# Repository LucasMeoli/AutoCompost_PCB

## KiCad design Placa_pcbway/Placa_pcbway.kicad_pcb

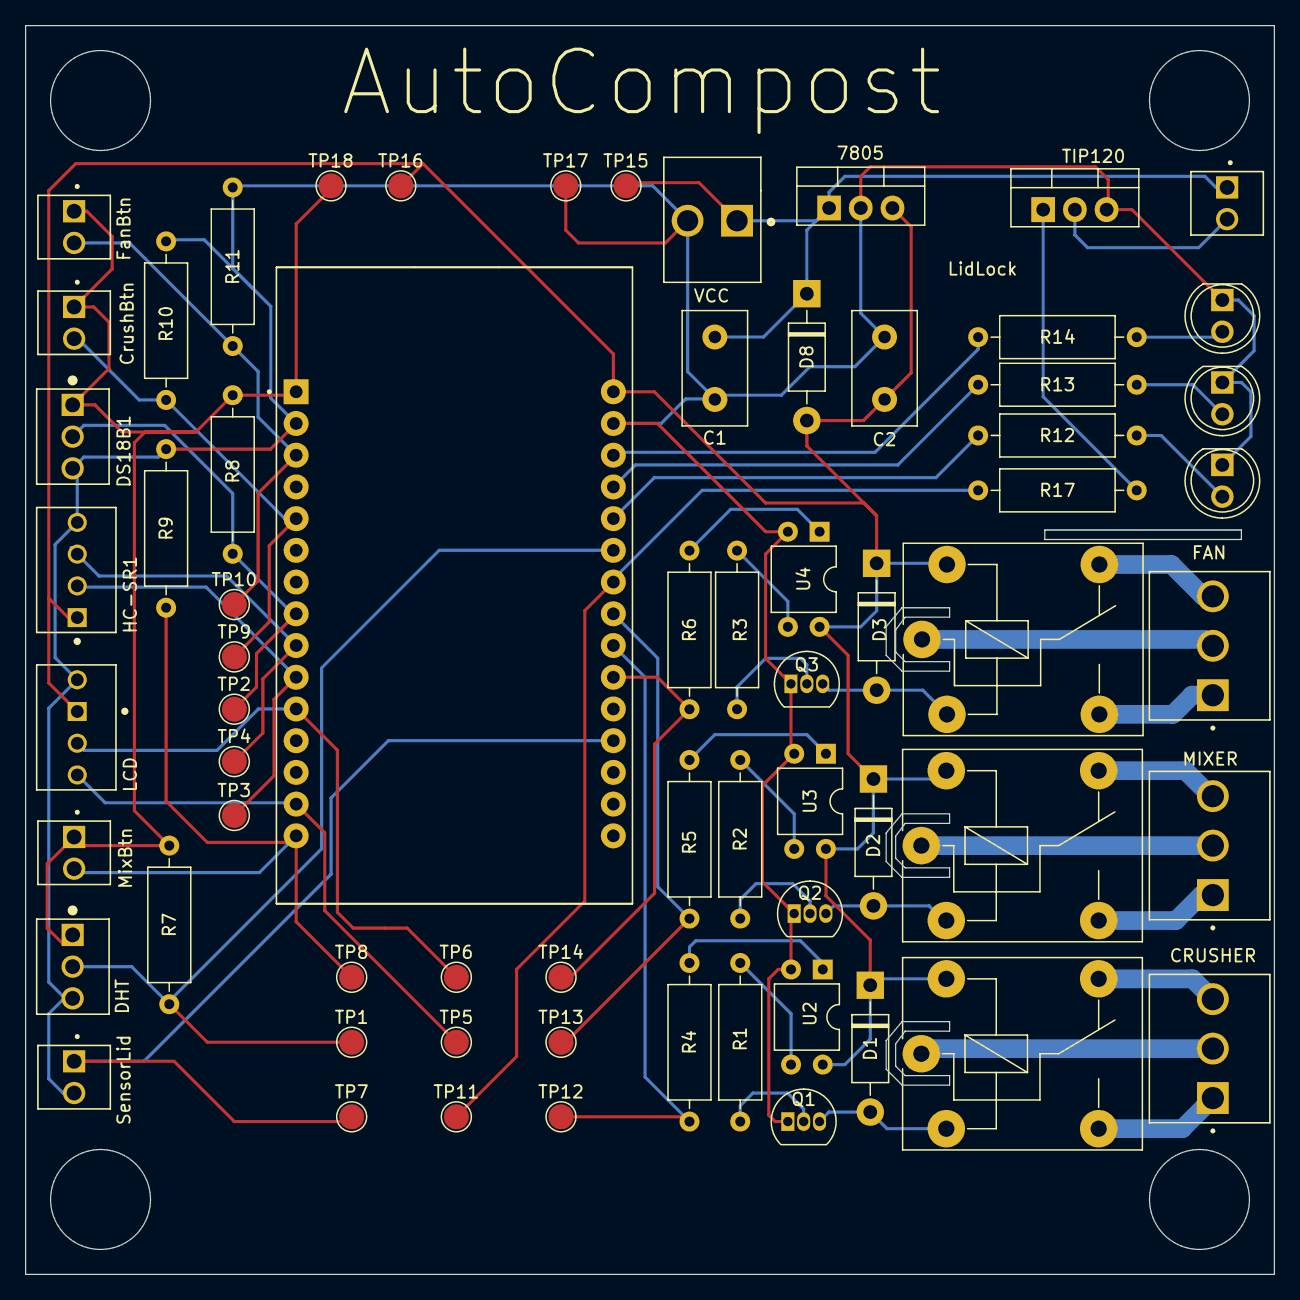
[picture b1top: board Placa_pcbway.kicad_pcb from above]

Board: 2 copper layers, 100.0 x 100.0 mm, 67 parts (0 on the bottom side), 47 nets.

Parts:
C1: 33nF; C_Disc_D9.0mm_W5.0mm_P5.00mm
C2: 100nF; C_Disc_D9.0mm_W5.0mm_P5.00mm
CrusherButton1: Molex 0.100; Molex_100_2pines
D1, D2, D3, D8: 1N4007; D_DO-41_SOD81_P10.16mm_Horizontal
D4, D5, D6: LED; LED_D5.0mm
DHT1: Molex 0.100; Molex_100_3pines
DS18B1: Molex 0.100; Molex_100_3pines
FanButton1: Molex 0.100; Molex_100_2pines
HC-SR1: Molex 0.100; Molex_100_4pines
J1, J2, J3: Molex 0.156; Molex_156_3pines
K1, K2, K3: FINDER-36.11; Relay_SPDT_Finder_36.11
LCD1: Molex 0.100; Molex_100_4pines
Lock1, Lock2: Molex 0.100; Molex_100_2pines
MixerButton1: Molex 0.100; Molex_100_2pines
Q1, Q2, Q3: 2N3904; TO-92_Inline
QLock1: TIP120; TO-220-3_Vertical
R1, R2, R3, R12, R13, R14: 220; R_Axial_DIN0309_L9.0mm_D3.2mm_P12.70mm_Horizontal
R4, R5, R6: 100; R_Axial_DIN0309_L9.0mm_D3.2mm_P12.70mm_Horizontal
R7, R8: 4k7; R_Axial_DIN0309_L9.0mm_D3.2mm_P12.70mm_Horizontal
R9, R10, R11: 10k; R_Axial_DIN0309_L9.0mm_D3.2mm_P12.70mm_Horizontal
R17: 2k2; R_Axial_DIN0309_L9.0mm_D3.2mm_P12.70mm_Horizontal
TP1, TP2, TP3, TP4, TP5, TP6, TP7, TP8, TP9, TP10, TP11, TP12, TP13, TP14, TP15, TP16, TP17, TP18: TestPoint; TestPoint_Pad_D2.0mm
U1: LM7805_TO220; TO-220-3_Vertical
U2, U3, U4: PC817; DIP-4_W7.62mm
U5: ESP32-DEVKIT-V1; MODULE_ESP32_DEVKIT_V1
Vext1: Molex 0.156; Molex_156_2pines

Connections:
5V: C2.1, D1.1 (K), D2.1 (K), D3.1 (K), D8.2 (A), HC-SR1.4, K1.A2, K2.A2, K3.A2, LCD1.2, TP16.1, U1.3 (VO), U2.4, U3.4, U4.4, U5.30 (VIN)
/3V3: CrusherButton1.1, DHT1.1, DS18B1.1, FanButton1.1, MixerButton1.1, R7.1, R8.1, TP18.1, U5.1 (3V3)
/Crusher: R4.1, TP12.1, U5.22 (D33)
/CrusherBtn: CrusherButton1.2, R10.2, TP9.1, U5.5 (D4)
/DHT: DHT1.2, R7.2, TP1.1, U5.25 (D27)
/DS18B20: DS18B1.2, R8.2, TP2.1, U5.8 (D5)
/Echo_HC-SR04: HC-SR1.2, TP4.1, U5.9 (D18)
/Fan: R6.1, TP14.1, U5.21 (D32)
/FanBtn: FanButton1.2, R11.2, TP10.1, U5.3 (D15)
/LCD_SCL: LCD1.4, TP5.1, U5.14 (D22)
/LCD_SDA: LCD1.3, TP6.1, U5.11 (D21)
/Led1: R12.2, U5.26 (D14)
/Led2: R13.2, U5.27 (D12)
/Led3: R14.2, U5.28 (D13)
/Lid: Lock1.1, TP7.1, U5.19 (D34)
/Lock: R17.2, TP11.1, U5.24 (D26)
/Mixer: R5.1, TP13.1, U5.23 (D25)
/MixerBtn: MixerButton1.2, R9.2, TP8.1, U5.15 (D23)
/Trig_HC-SR04: HC-SR1.3, TP3.1, U5.10 (D19)
/VCC: C1.1, D8.1 (K), Lock2.1, TP15.1, U1.1 (VI), Vext1.1
GND: C1.2, C2.2, D4.1 (K), D5.1 (K), D6.1 (K), DHT1.3, DS18B1.3, HC-SR1.1, LCD1.1, Lock1.2, Q1.1 (E), Q2.1 (E), Q3.1 (E), QLock1.3 (E), R9.1, R10.1, R11.1, TP17.1, U1.2 (GND), U2.2, U3.2, U4.2, U5.2 (GND), U5.29 (GND), Vext1.2
unnamed: D1.2 (A), K1.A1, Q1.3 (C)
unnamed: D2.2 (A), K2.A1, Q2.3 (C)
unnamed: D3.2 (A), K3.A1, Q3.3 (C)
unnamed: D4.2 (A), R12.1
unnamed: D5.2 (A), R13.1
unnamed: D6.2 (A), R14.1
unnamed: J1.1, K1.14
unnamed: J1.2, K1.11
unnamed: J1.3, K1.12
unnamed: J2.1, K2.14
unnamed: J2.2, K2.11
unnamed: J2.3, K2.12
unnamed: J3.1, K3.14
unnamed: J3.2, K3.11
unnamed: J3.3, K3.12
unnamed: Q1.2 (B), R1.2
unnamed: Q2.2 (B), R2.2
unnamed: Q3.2 (B), R3.2
unnamed: QLock1.1 (B), R17.1
unnamed: Lock2.2, QLock1.2 (C)
unnamed: R1.1, U2.3
unnamed: R2.1, U3.3
unnamed: R3.1, U4.3
unnamed: R4.2, U2.1
unnamed: R5.2, U3.1
unnamed: R6.2, U4.1

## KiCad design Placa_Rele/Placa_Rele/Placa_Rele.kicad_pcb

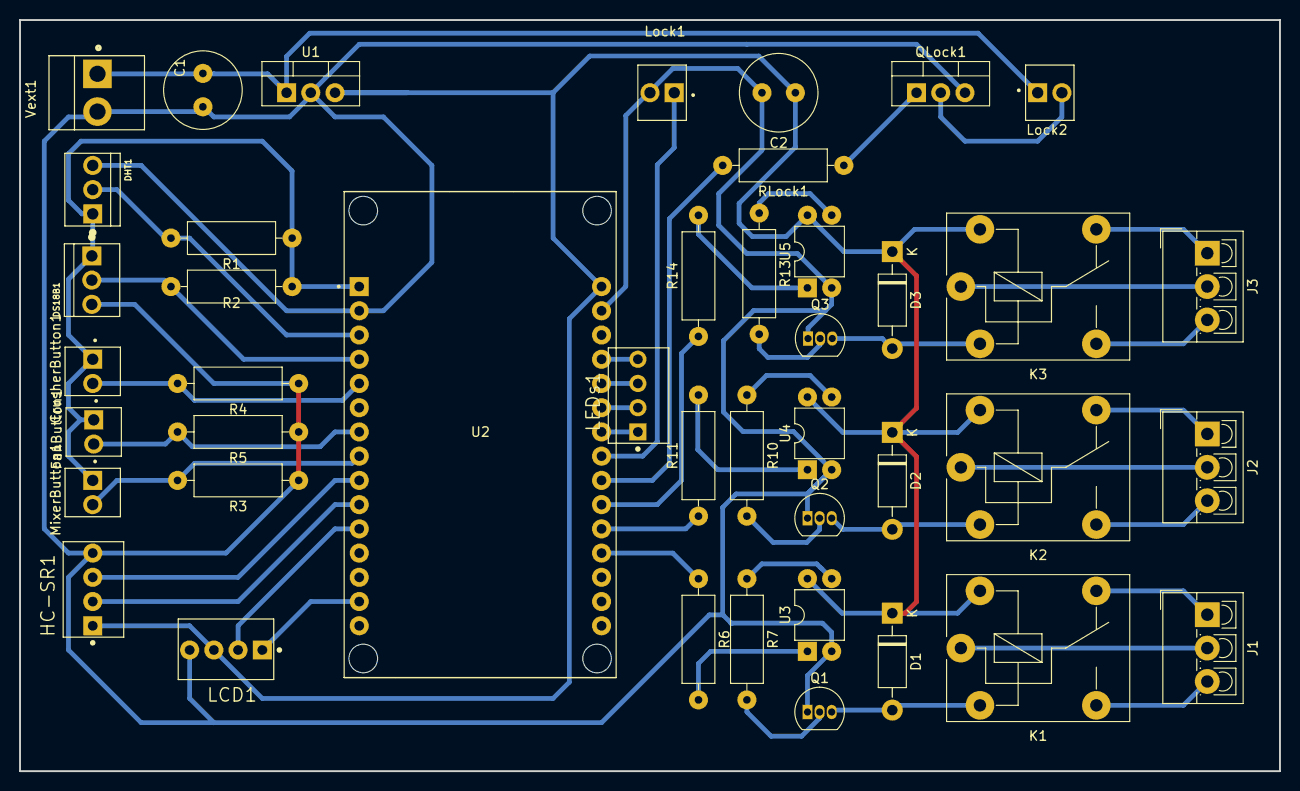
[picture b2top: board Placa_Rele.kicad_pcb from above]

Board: 2 copper layers, 132.1 x 78.7 mm, 43 parts (0 on the bottom side), 45 nets.

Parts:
C1: 33nF; C_Radial_D8.0mm_H7.0mm_P3.50mm
C2: 100nF; C_Radial_D8.0mm_H7.0mm_P3.50mm
CrusherButton1: Molex 0.100; Molex_100_2pines
D1, D2, D3: 1N4007; D_DO-41_SOD81_P10.16mm_Horizontal
DHT1: Molex 0.100; Molex_100_3pines
DS18B1: Molex 0.100; Molex_100_3pines
FanButton1: Molex 0.100; Molex_100_2pines
HC-SR1: Molex 0.100; Molex_100_4pines
J1: Screw_Terminal_Crusher1; TerminalBlock_4Ucon_1x03_P3.50mm_Vertical
J2: MixerScrewTerminal1; TerminalBlock_4Ucon_1x03_P3.50mm_Vertical
J3: FanScrewTerminal1; TerminalBlock_4Ucon_1x03_P3.50mm_Vertical
K1, K2, K3: FINDER-36.11; Relay_SPDT_Finder_36.11
LCD1: Molex 0.100; Molex_100_4pines
LEDs1: Molex 0.100; Molex_100_4pines
Lock1, Lock2: Molex 0.100; Molex_100_2pines
MixerButton1: Molex 0.100; Molex_100_2pines
Q1, Q2, Q3: 2N3904; TO-92_Inline
QLock1: TIP120; TO-220-3_Vertical
R1, R2: 4k7; R_Axial_DIN0309_L9.0mm_D3.2mm_P12.70mm_Horizontal
R3, R4, R5: 10k; R_Axial_DIN0309_L9.0mm_D3.2mm_P12.70mm_Horizontal
R6, R11, R14: 100; R_Axial_DIN0309_L9.0mm_D3.2mm_P12.70mm_Horizontal
R7, R10, R13: 220; R_Axial_DIN0309_L9.0mm_D3.2mm_P12.70mm_Horizontal
RLock1: 2k2; R_Axial_DIN0309_L9.0mm_D3.2mm_P12.70mm_Horizontal
U1: LM7805_TO220; TO-220-3_Vertical
U2: ESP32-DEVKIT-V1; MODULE_ESP32_DEVKIT_V1
U3, U4, U5: PC817; DIP-4_W7.62mm
Vext1: Molex 0.156; Molex_156_2pines

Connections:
5V: C2.1, D1.1 (K), D2.1 (K), D3.1 (K), HC-SR1.1, K1.A2, K2.A2, K3.A2, LCD1.3, U1.3 (VO), U2.30 (VIN), U3.4, U4.4, U5.4
/3V3: CrusherButton1.1, DHT1.1, DS18B1.1, FanButton1.1, MixerButton1.1, R1.1, R2.1, U2.1 (3V3)
/Crusher: R6.1, U2.19 (D34)
/CrusherBtn: CrusherButton1.2, R4.2, U2.5 (D4)
/DHT: DHT1.2, R1.2, U2.3 (D15)
/DS18B20: DS18B1.2, R2.2, U2.4 (D2)
/Echo_HC-SR04: HC-SR1.3, U2.9 (D18)
/Fan: R14.1, U2.21 (D32)
/FanBtn: FanButton1.2, R5.2, U2.7 (TX2)
/LCD_SCL: LCD1.1, U2.14 (D22)
/LCD_SDA: LCD1.2, U2.11 (D21)
/Led1: LEDs1.1, U2.24 (D26)
/Led2: LEDs1.2, U2.25 (D27)
/Led3: LEDs1.3, U2.26 (D14)
/Led4: LEDs1.4, U2.27 (D12)
/Lid: Lock1.1, U2.23 (D25)
/Lock: RLock1.2, U2.22 (D33)
/Mixer: R11.1, U2.20 (D35)
/MixerBtn: MixerButton1.2, R3.2, U2.8 (D5)
/Trig_HC-SR04: HC-SR1.2, U2.10 (D19)
/VCC: C1.1, Lock2.1, U1.1 (VI), Vext1.1
GND: C1.2, C2.2, DHT1.3, DS18B1.3, HC-SR1.4, LCD1.4, Lock1.2, Q1.1 (E), Q2.1 (E), Q3.1 (E), QLock1.3 (E), R3.1, R4.1, R5.1, U1.2 (GND), U2.2 (GND), U2.29 (GND), U3.2, U4.2, U5.2, Vext1.2
unnamed: D1.2 (A), K1.A1, Q1.3 (C)
unnamed: D2.2 (A), K2.A1, Q2.3 (C)
unnamed: D3.2 (A), K3.A1, Q3.3 (C)
unnamed: J1.1, K1.12
unnamed: J1.2, K1.11
unnamed: J1.3, K1.14
unnamed: J2.1, K2.12
unnamed: J2.2, K2.11
unnamed: J2.3, K2.14
unnamed: J3.1, K3.12
unnamed: J3.2, K3.11
unnamed: J3.3, K3.14
unnamed: Q1.2 (B), R7.2
unnamed: Q2.2 (B), R10.2
unnamed: Q3.2 (B), R13.2
unnamed: QLock1.1 (B), RLock1.1
unnamed: Lock2.2, QLock1.2 (C)
unnamed: R6.2, U3.1
unnamed: R7.1, U3.3
unnamed: R10.1, U4.3
unnamed: R11.2, U4.1
unnamed: R13.1, U5.3
unnamed: R14.2, U5.1

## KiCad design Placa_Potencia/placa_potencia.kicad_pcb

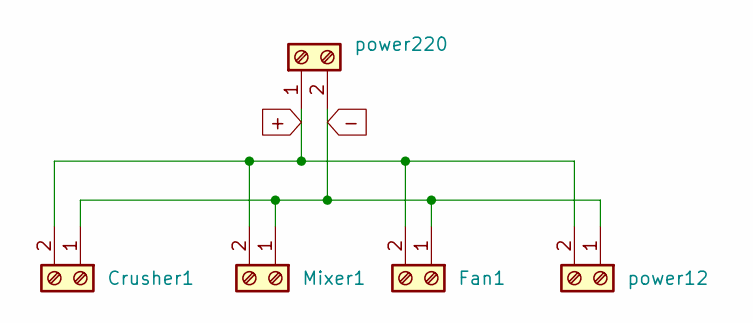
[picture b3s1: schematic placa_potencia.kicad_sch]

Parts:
Crusher1: Screw_Terminal_01x02; TerminalBlock_4Ucon_1x02_P3.50mm_Vertical
Fan1: Screw_Terminal_01x02; TerminalBlock_4Ucon_1x02_P3.50mm_Vertical
Mixer1: Screw_Terminal_01x02; TerminalBlock_4Ucon_1x02_P3.50mm_Vertical
power12, power220: Screw_Terminal_01x02; TerminalBlock_4Ucon_1x02_P3.50mm_Vertical

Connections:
+: Crusher1.2, Fan1.2, Mixer1.2, power12.2, power220.1
-: Crusher1.1, Fan1.1, Mixer1.1, power12.1, power220.2

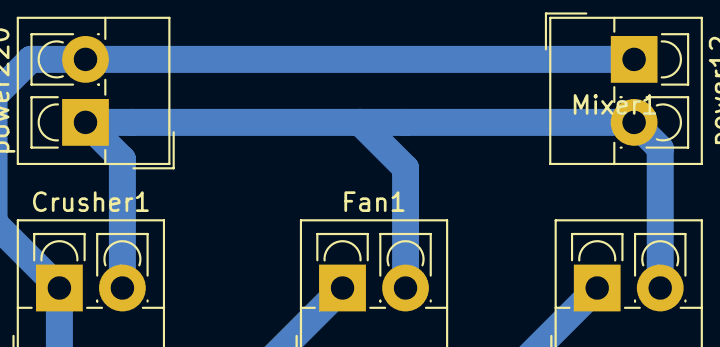
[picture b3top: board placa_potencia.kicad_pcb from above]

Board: 2 copper layers, 5 parts (0 on the bottom side), 2 nets.

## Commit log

2023-10-11 Initialization of PCB proyect
2023-10-13 Agregado de botones
2023-10-15 Agregado de esquematico con rele
2023-10-16 Primero Version de PCB con PCB_rele
    Primer PCB terminado, los componentes no estan en su posicion final.
    El principal problema fue la conexion de 5V, 3v3 y GND en los conectores
    del ultrasonico, LCD y DHT.
2023-10-16 Modificacion de PCB
    Se cambiaron los ordenes de los GPIO asi DHT y DS18B estaban en los
    primeros GPIOS y facilitaba el ruteo.
2023-10-22 Placa final con reles pero sin LEDS
2023-10-22 Placa de potencia agregada
    Falta definir correctamente los conectores, acutalmente solo tiene una bornera tipica de PCB
2023-10-25 Placa de potencia terminada con borneras
2023-11-04 feat: Agregado de placa para pcbway
2023-11-04 Placa Pcbway terminada
    Se agrandaron los agujeros correspondientes, se agregaron los agujeros de placa y el DRC pass
2023-11-05 Placa pcbway terminada sin plano de tierra
2023-11-05 Placa con plano de tierra
2023-11-05 Correccion Fan Button
2023-11-05 Cambio de pin Fan Button
2023-11-05 Placa terminada sin plano
    Placa terminada:
    - Disñeos 3D agregados
    - TP y Molex alineados
    - Conexiones terminadas
2023-11-05 Plano de tierra agregado
2023-11-05 Placa finalizada con plano de tierra
2023-11-05 Modificacion de una pista
2023-11-06 feat: Modificacion de capacitores de 7805
